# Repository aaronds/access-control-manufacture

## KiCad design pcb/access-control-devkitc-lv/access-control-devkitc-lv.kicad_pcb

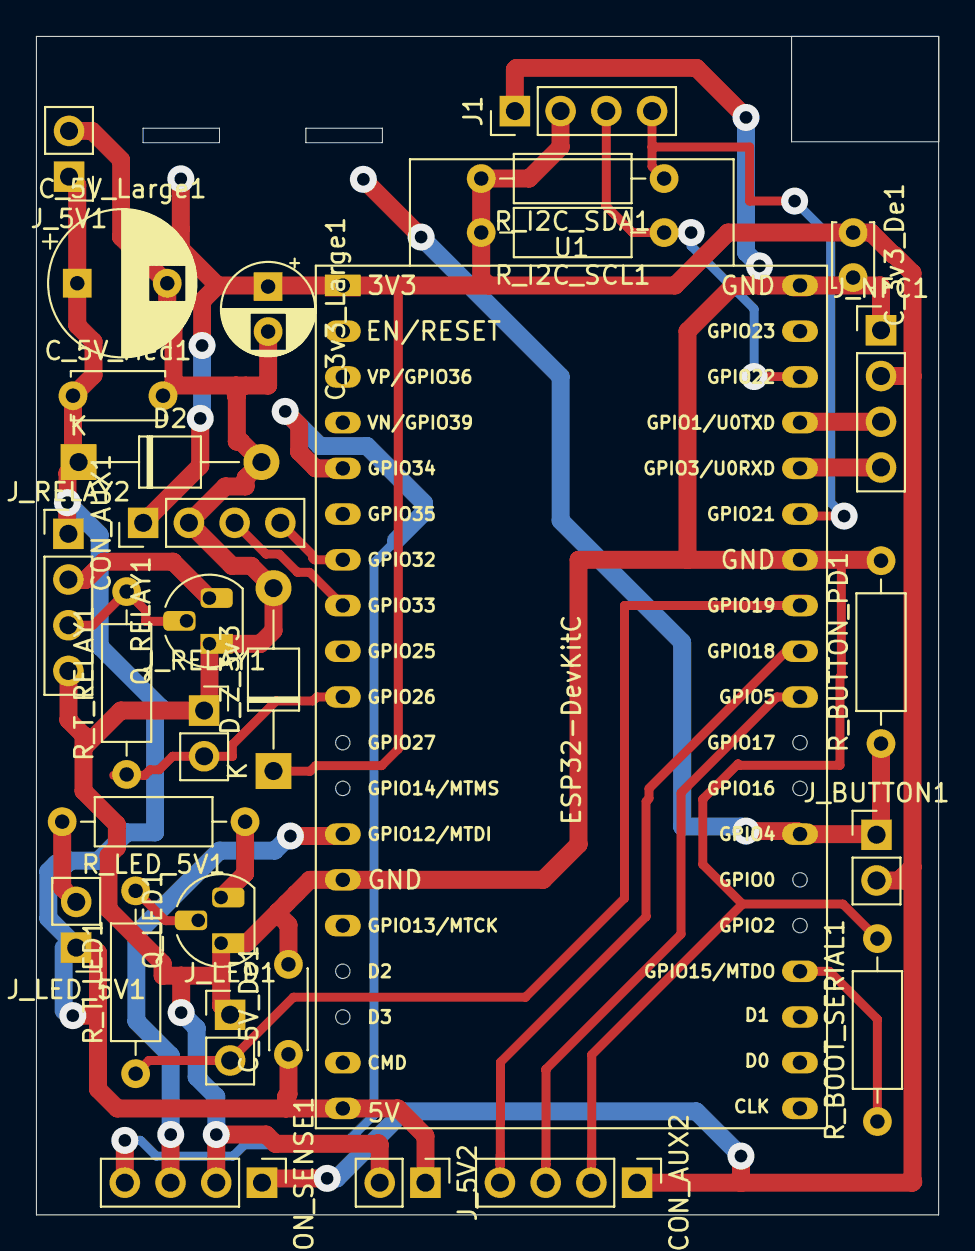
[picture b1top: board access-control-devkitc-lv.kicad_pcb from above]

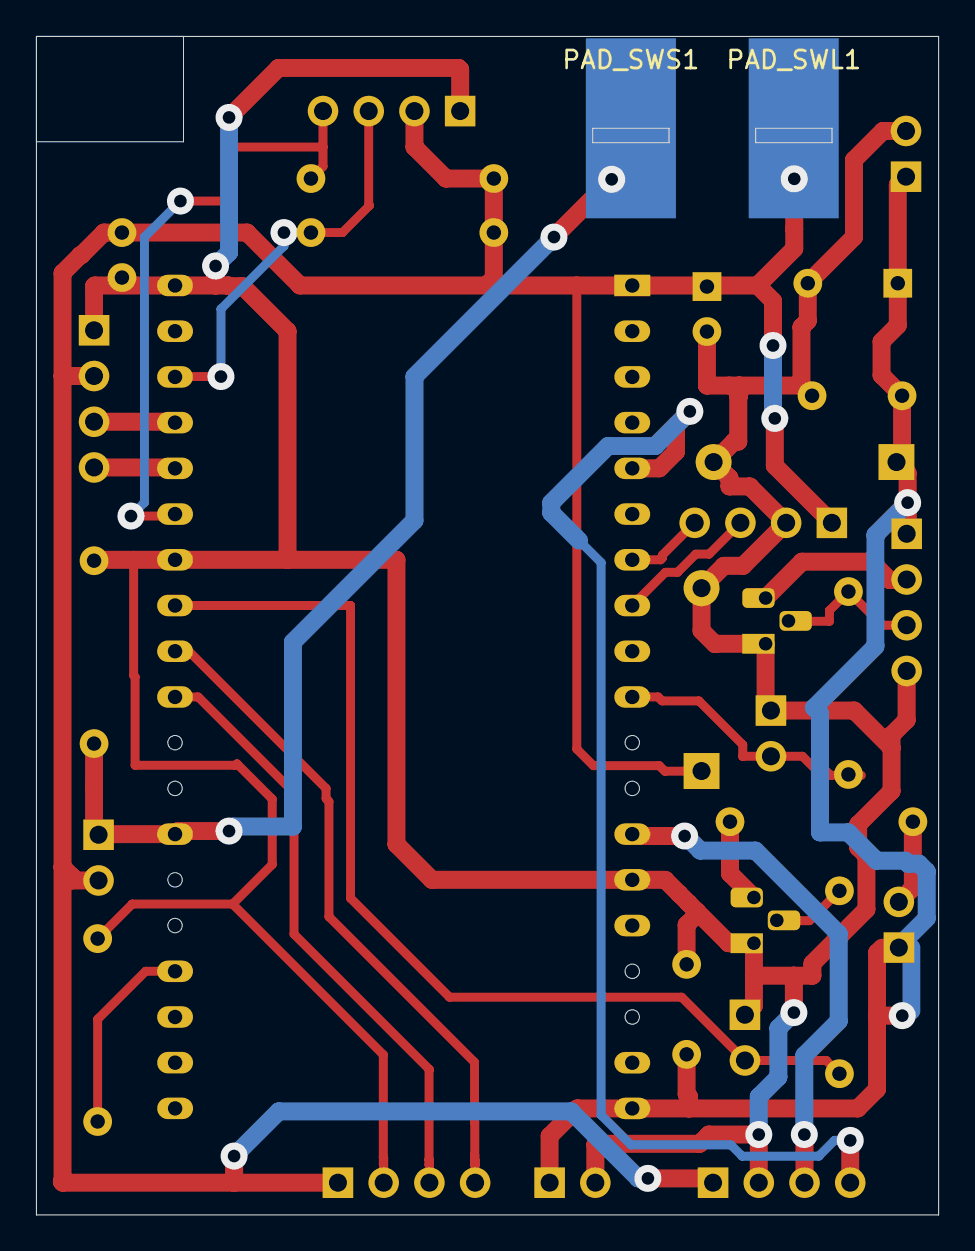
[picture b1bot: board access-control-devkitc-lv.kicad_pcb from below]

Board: 2 copper layers, 50.1 x 65.5 mm, 31 parts (2 on the bottom side), 20 nets.

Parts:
CON_AUX1, CON_AUX2: Conn_01x04_Socket; PinHeader_1x04_P2.54mm_Vertical
CON_SENSE1: Conn_01x04_Socket; PinHeader_1x04_P2.54mm_Vertical
C_3v3_De1: C; C_Disc_D3.4mm_W2.1mm_P2.50mm
C_3v3_Large1: C_Polarized; CP_Radial_D5.0mm_P2.50mm
C_5V_De1: C; C_Disc_D4.3mm_W1.9mm_P5.00mm
C_5V_Large1: 1000uf; CP_Radial_D8.0mm_P5.00mm
C_5V_Med1: C; C_Disc_D5.0mm_W2.5mm_P5.00mm
D2: D_Zener; D_T-1_P10.16mm_Horizontal
D_Z_3v3: D_Zener; D_T-1_P10.16mm_Horizontal
J1: CON_I2C; PinHeader_1x04_P2.54mm_Vertical
J_5V1, J_5V2: Conn_01x02_Socket; PinHeader_1x02_P2.54mm_Vertical
J_BUTTON1: Conn_01x02_Socket; PinHeader_1x02_P2.54mm_Vertical
J_LED1: Conn_01x02_Socket; PinHeader_1x02_P2.54mm_Vertical
J_LED_5V1: Conn_01x02_Socket; PinHeader_1x02_P2.54mm_Vertical
J_NFC1: Conn_01x04_Socket; PinHeader_1x04_P2.54mm_Vertical
J_RELAY1: Conn_01x02_Socket; PinSocket_1x02_P2.54mm_Vertical
J_RELAY2: Conn_01x02_Socket; PinHeader_1x04_P2.54mm_Vertical
PAD_SWL1: Conn_01x01_Female; SolderWirePad_1x01_SMD_5x10mm
PAD_SWS1: Conn_01x01_Female; SolderWirePad_1x01_SMD_5x10mm
Q_LED1: PN2222A; TO-92L_HandSolder
Q_RELAY1: PN2222A; TO-92L_HandSolder
R_BOOT_SERIAL1: 10kR; R_Axial_DIN0207_L6.3mm_D2.5mm_P10.16mm_Horizontal
R_BUTTON_PD1: 10kR; R_Axial_DIN0207_L6.3mm_D2.5mm_P10.16mm_Horizontal
R_I2C_SCL1, R_I2C_SDA1: R; R_Axial_DIN0207_L6.3mm_D2.5mm_P10.16mm_Horizontal
R_LED_5V1: 330R; R_Axial_DIN0207_L6.3mm_D2.5mm_P10.16mm_Horizontal
R_T_LED1: 560R; R_Axial_DIN0207_L6.3mm_D2.5mm_P10.16mm_Horizontal
R_T_RELAY1: 560R; R_Axial_DIN0207_L6.3mm_D2.5mm_P10.16mm_Horizontal
U1: ESP32-DevKitC

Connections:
+3V3: CON_AUX1.1, CON_AUX2.1, CON_SENSE1.1, C_3v3_De1.1, C_3v3_Large1.1, D_Z_3v3.1 (K), J1.2, J_BUTTON1.2, J_NFC1.2, PAD_SWL1.1, R_I2C_SCL1.2, R_I2C_SDA1.2, U1.1 (3V3)
+5V: C_5V_De1.1, C_5V_Large1.1, C_5V_Med1.1, D2.1 (K), J_5V1.1, J_5V2.1, J_LED_5V1.1, J_RELAY2.1, U1.19 (5V)
GND: CON_AUX1.2, CON_AUX2.2, CON_SENSE1.2, C_3v3_De1.2, C_3v3_Large1.2, C_5V_De1.2, C_5V_Large1.2, C_5V_Med1.2, D2.2 (A), D_Z_3v3.2 (A), J1.1, J_5V1.2, J_5V2.2, J_LED1.1, J_NFC1.1, J_RELAY1.1, J_RELAY2.4, Q_LED1.1 (E), Q_RELAY1.1 (E), R_BOOT_SERIAL1.2, R_BUTTON_PD1.2, U1.14 (GND), U1.32 (GND), U1.38 (GND)
unnamed: CON_AUX1.3, U1.8 (32K_XN/GPIO33/ADC1_CH5)
unnamed: CON_AUX1.4, U1.7 (32K_XP/GPIO32/ADC1_CH4)
unnamed: CON_SENSE1.3, U1.13 (MTDI/GPIO12/ADC2_CH5)
unnamed: CON_SENSE1.4, U1.5 (VDET_1/GPIO34/ADC1_CH6)
unnamed: J1.3, R_I2C_SCL1.1, U1.36 (GPIO22)
unnamed: J1.4, R_I2C_SDA1.1, U1.33 (GPIO21)
unnamed: J_BUTTON1.1, PAD_SWS1.1, R_BUTTON_PD1.1, U1.26 (ADC2_CH0/GPIO4)
unnamed: J_LED1.2, R_T_LED1.1, U1.31 (GPIO19)
unnamed: J_LED_5V1.2, R_LED_5V1.2
unnamed: J_NFC1.3, U1.35 (U0TXD/GPIO1)
unnamed: J_NFC1.4, U1.34 (U0RXD/GPIO3)
unnamed: J_RELAY1.2, R_T_RELAY1.1, U1.10 (DAC_2/ADC2_CH9/GPIO26)
unnamed: J_RELAY2.2, Q_RELAY1.3 (C)
unnamed: J_RELAY2.3, Q_RELAY1.2 (B), R_T_RELAY1.2
unnamed: Q_LED1.2 (B), R_T_LED1.2
unnamed: Q_LED1.3 (C), R_LED_5V1.1
unnamed: R_BOOT_SERIAL1.1, U1.23 (MTDO/GPIO15/ADC2_CH3)

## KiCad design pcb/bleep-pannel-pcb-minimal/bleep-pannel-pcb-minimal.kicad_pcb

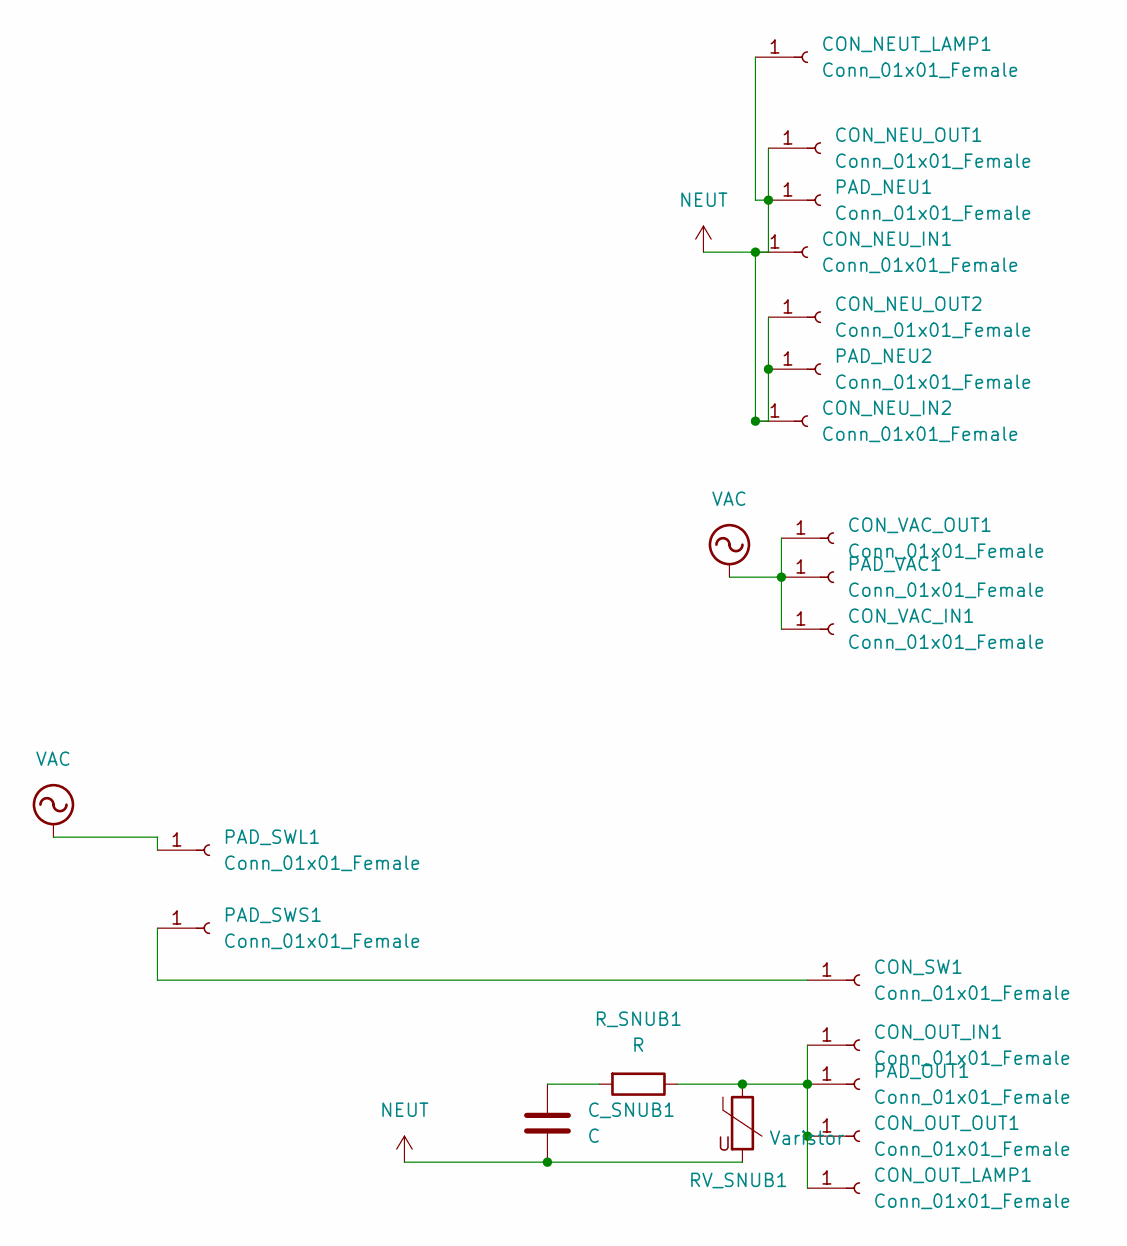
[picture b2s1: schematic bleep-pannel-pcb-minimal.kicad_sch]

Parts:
CON_NEUT_LAMP1: Conn_01x01_Female; PinHeader_1x01_P2.54mm_Vertical
CON_NEU_IN1, CON_NEU_IN2: Conn_01x01_Female; SolderWire-0.75sqmm_1x01_D1.25mm_OD3.5mm
CON_NEU_OUT1, CON_NEU_OUT2: Conn_01x01_Female; SolderWire-0.75sqmm_1x01_D1.25mm_OD3.5mm
CON_OUT_IN1: Conn_01x01_Female; SolderWire-0.75sqmm_1x01_D1.25mm_OD3.5mm
CON_OUT_LAMP1: Conn_01x01_Female; SolderWire-0.75sqmm_1x01_D1.25mm_OD3.5mm
CON_OUT_OUT1: Conn_01x01_Female; SolderWire-0.75sqmm_1x01_D1.25mm_OD3.5mm
CON_SW1: Conn_01x01_Female; PinHeader_1x01_P2.54mm_Vertical
CON_VAC_IN1: Conn_01x01_Female; SolderWire-0.75sqmm_1x01_D1.25mm_OD3.5mm
CON_VAC_OUT1: Conn_01x01_Female; SolderWire-0.75sqmm_1x01_D1.25mm_OD3.5mm
C_SNUB1: C; CP_Axial_L10.0mm_D6.0mm_P15.00mm_Horizontal
PAD_NEU1, PAD_NEU2: Conn_01x01_Female; SolderWirePad_1x01_SMD_5x10mm
PAD_OUT1: Conn_01x01_Female; SolderWirePad_1x01_SMD_5x10mm
PAD_SWL1: Conn_01x01_Female; SolderWirePad_1x01_SMD_5x10mm
PAD_SWS1: Conn_01x01_Female; SolderWirePad_1x01_SMD_5x10mm
PAD_VAC1: Conn_01x01_Female; SolderWirePad_1x01_SMD_5x10mm
RV_SNUB1: Varistor; RV_Disc_D12mm_W3.9mm_P7.5mm
R_SNUB1: R; R_Axial_DIN0617_L17.0mm_D6.0mm_P20.32mm_Horizontal

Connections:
NEUT: CON_NEUT_LAMP1.1, CON_NEU_IN1.1, CON_NEU_IN2.1, CON_NEU_OUT1.1, CON_NEU_OUT2.1, C_SNUB1.2, PAD_NEU1.1, PAD_NEU2.1, RV_SNUB1.2
unnamed: CON_OUT_IN1.1, CON_OUT_LAMP1.1, CON_OUT_OUT1.1, PAD_OUT1.1, RV_SNUB1.1, R_SNUB1.1
unnamed: CON_SW1.1, PAD_SWS1.1
unnamed: C_SNUB1.1, R_SNUB1.2
VAC: CON_VAC_IN1.1, CON_VAC_OUT1.1, PAD_SWL1.1, PAD_VAC1.1

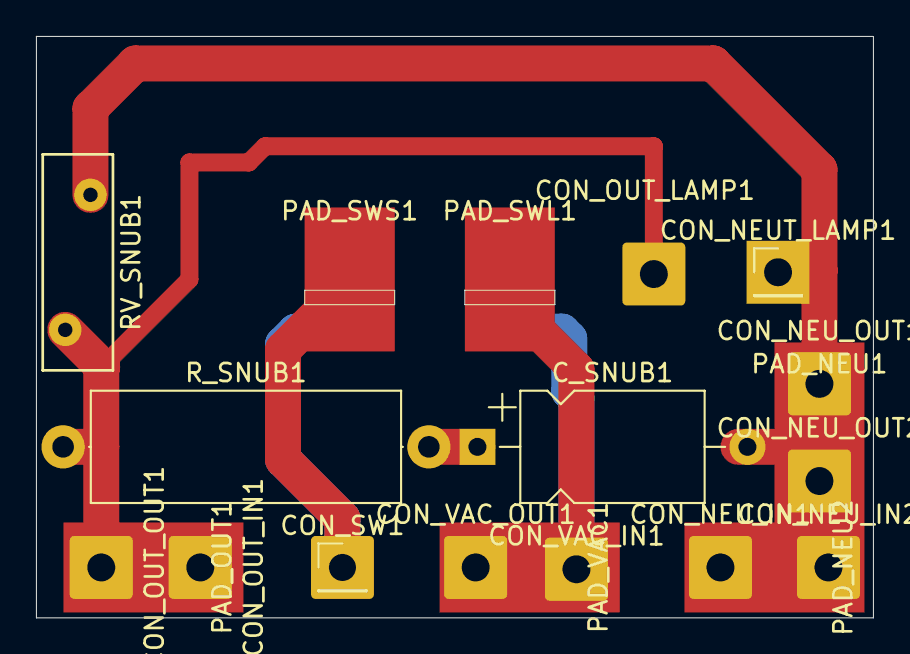
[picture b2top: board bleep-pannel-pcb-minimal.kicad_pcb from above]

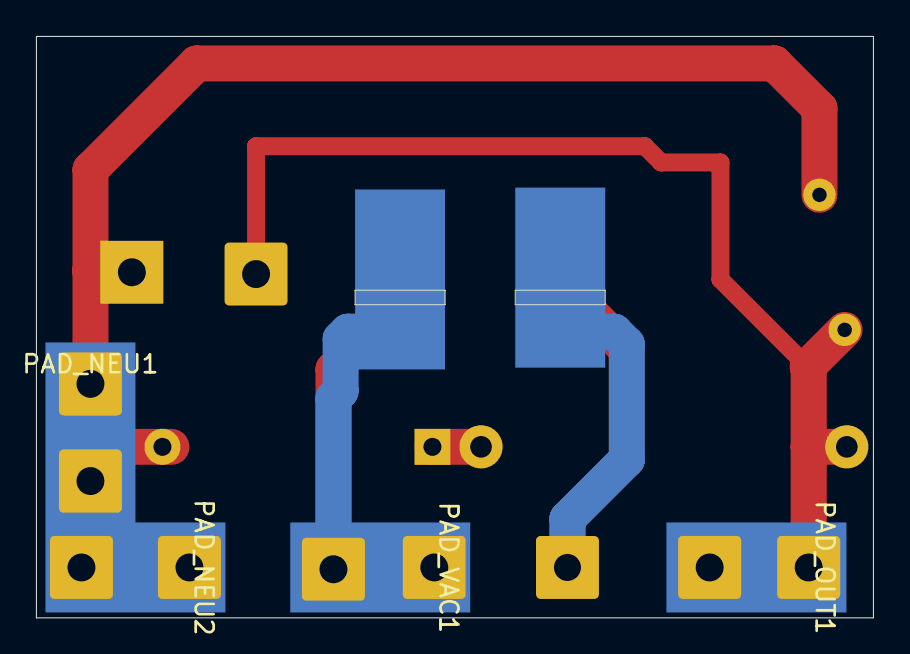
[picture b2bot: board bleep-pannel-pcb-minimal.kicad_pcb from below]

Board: 2 copper layers, 46.5 x 32.3 mm, 24 parts (4 on the bottom side), 5 nets.

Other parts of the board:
PAD_NEU1#2, PAD_NEU2#2: Conn_01x01_Female; SolderWirePad_1x01_SMD_5x10mm
PAD_OUT1#2: Conn_01x01_Female; SolderWirePad_1x01_SMD_5x10mm
PAD_VAC1#2: Conn_01x01_Female; SolderWirePad_1x01_SMD_5x10mm

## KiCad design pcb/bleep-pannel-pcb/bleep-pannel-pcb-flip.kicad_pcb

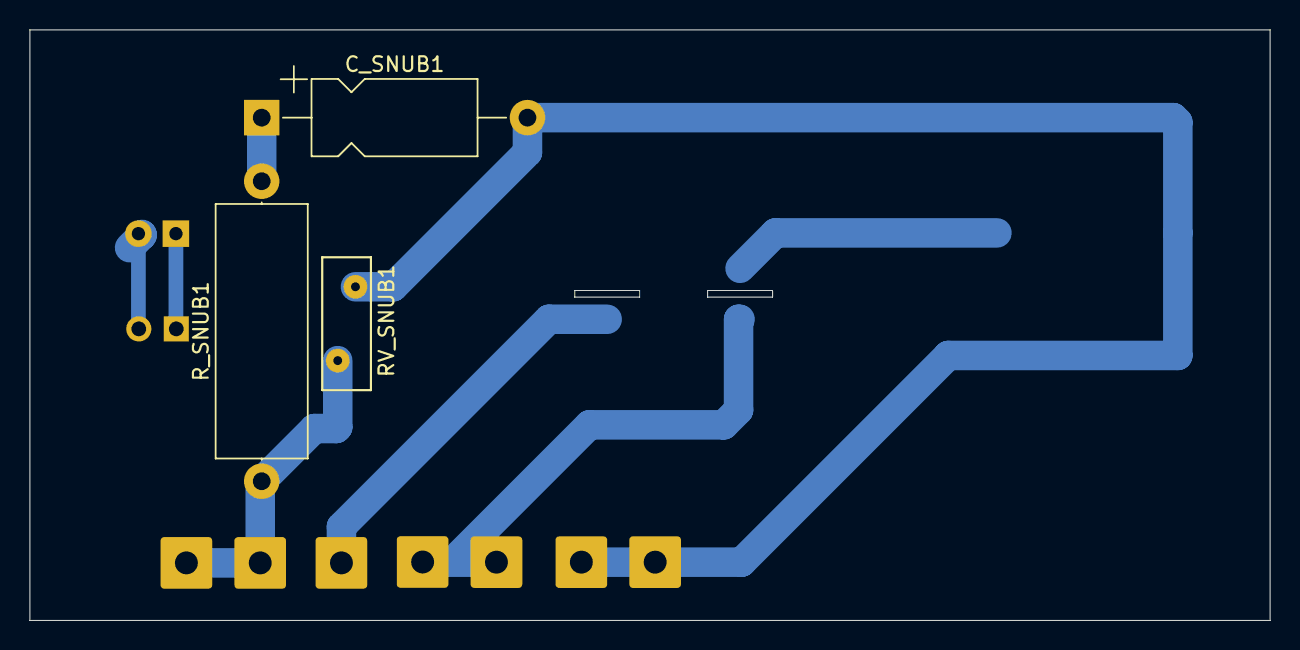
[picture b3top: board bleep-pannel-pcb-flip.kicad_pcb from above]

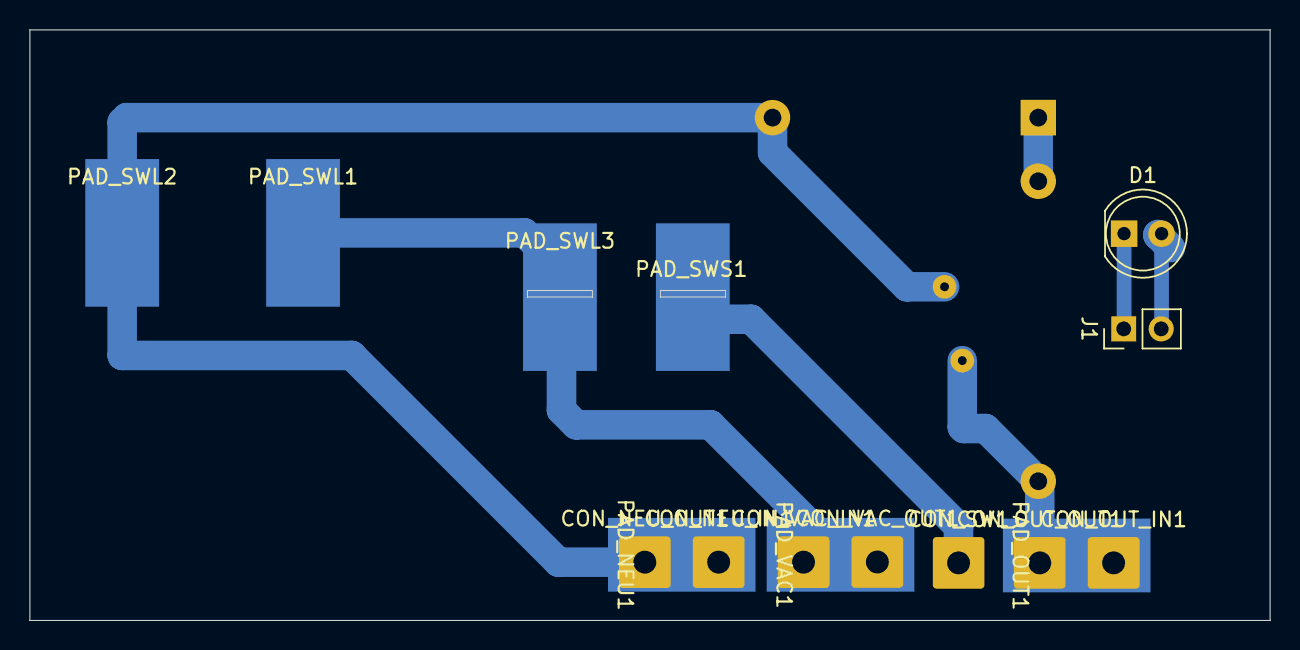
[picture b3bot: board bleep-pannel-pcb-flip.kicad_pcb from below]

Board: 2 copper layers, 84.0 x 40.0 mm, 19 parts (16 on the bottom side), 7 nets.

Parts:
CON_NEU_IN1: Conn_01x01_Female; SolderWire-0.75sqmm_1x01_D1.25mm_OD3.5mm
CON_NEU_OUT1: Conn_01x01_Female; SolderWire-0.75sqmm_1x01_D1.25mm_OD3.5mm
CON_OUT_IN1: Conn_01x01_Female; SolderWire-0.75sqmm_1x01_D1.25mm_OD3.5mm
CON_OUT_OUT1: Conn_01x01_Female; SolderWire-0.75sqmm_1x01_D1.25mm_OD3.5mm
CON_SW1: Conn_01x01_Female; SolderWire-0.75sqmm_1x01_D1.25mm_OD3.5mm
CON_VAC_IN1: Conn_01x01_Female; SolderWire-0.75sqmm_1x01_D1.25mm_OD3.5mm
CON_VAC_OUT1: Conn_01x01_Female; SolderWire-0.75sqmm_1x01_D1.25mm_OD3.5mm
C_SNUB1: C; CP_Axial_L11.0mm_D5.0mm_P18.00mm_Horizontal
D1: LED; LED_D5.0mm
J1: CON_LED; PinHeader_1x02_P2.54mm_Vertical
PAD_NEU1: Conn_01x01_Female; SolderWirePad_1x01_SMD_5x10mm
PAD_OUT1: Conn_01x01_Female; SolderWirePad_1x01_SMD_5x10mm
PAD_SWL1, PAD_SWL2, PAD_SWL3: Conn_01x01_Female; SolderWirePad_1x01_SMD_5x10mm
PAD_SWS1: Conn_01x01_Female; SolderWirePad_1x01_SMD_5x10mm
PAD_VAC1: Conn_01x01_Female; SolderWirePad_1x01_SMD_5x10mm
RV_SNUB1: Varistor; RV_Disc_D9mm_W3.3mm_P5mm
R_SNUB1: R; R_Axial_DIN0617_L17.0mm_D6.0mm_P20.32mm_Horizontal

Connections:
NEUT: CON_NEU_IN1.1, CON_NEU_OUT1.1, C_SNUB1.2, PAD_NEU1.1, PAD_SWL2.1, RV_SNUB1.2
unnamed: CON_OUT_IN1.1, CON_OUT_OUT1.1, PAD_OUT1.1, RV_SNUB1.1, R_SNUB1.1
unnamed: CON_SW1.1, PAD_SWS1.1
unnamed: C_SNUB1.1, R_SNUB1.2
unnamed: D1.2 (A), J1.2
unnamed: D1.1 (K), J1.1
VAC: CON_VAC_IN1.1, CON_VAC_OUT1.1, PAD_SWL1.1, PAD_SWL3.1, PAD_VAC1.1
